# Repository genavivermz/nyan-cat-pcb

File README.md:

# nyancat PCB ₍^. .^₎⟆
made with KiCad; flat components for more lightweight use (as keychain or for general decoration!)

# design
- ordering with white solder mask + black silkscreen
- shiny tail design, made with decorative copper tracks + lines stacked on top
- colorful lights running a chasing pattern (powered by ATtiny10 microcontroller)

# preview

&nbsp

# schematics

# pcb editor

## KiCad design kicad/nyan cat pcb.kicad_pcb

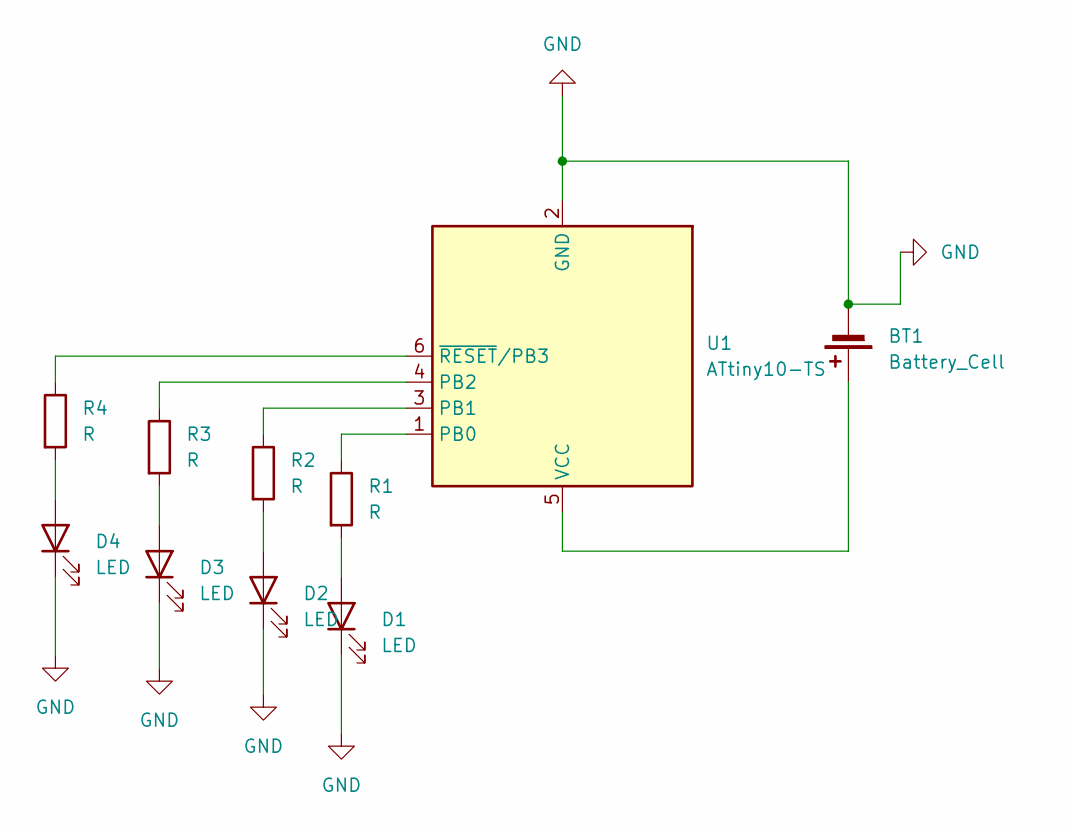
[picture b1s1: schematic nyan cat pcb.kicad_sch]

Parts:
BT1: Battery_Cell; BatteryHolder_LINX_BAT-HLD-012-SMT
D1, D2, D3, D4: LED; LED_0603_1608Metric
R1, R2, R3, R4: R; R_0603_1608Metric
U1: ATtiny10-TS; SOT-23-6

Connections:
GND: BT1.2 (-), D1.1 (K), D2.1 (K), D3.1 (K), D4.1 (K), U1.2 (GND)
unnamed: BT1.1 (+), U1.5 (VCC)
unnamed: D1.2 (A), R1.2
unnamed: D2.2 (A), R2.2
unnamed: D3.2 (A), R3.2
unnamed: D4.2 (A), R4.2
unnamed: R1.1, U1.1 (PB0)
unnamed: R2.1, U1.3 (PB1)
unnamed: R3.1, U1.4 (PB2)
unnamed: R4.1, U1.6 (~RESET/PB3)

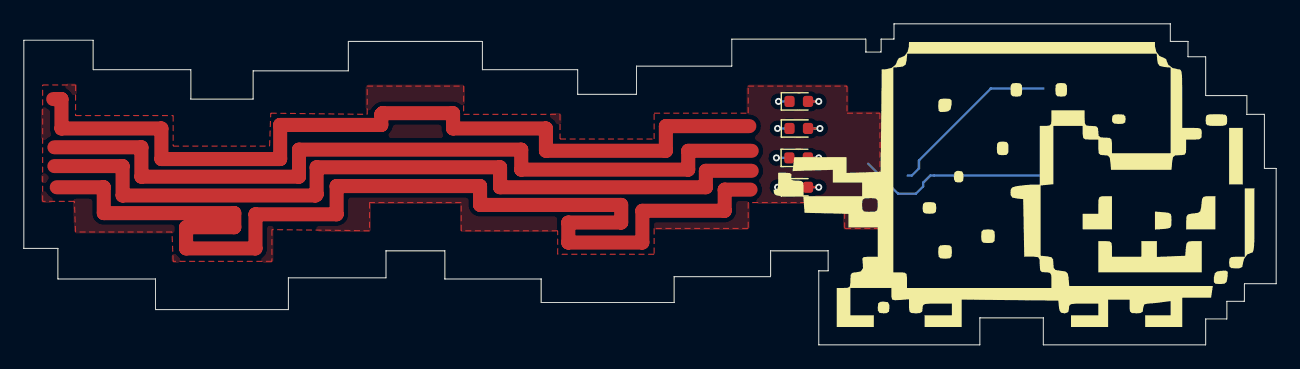
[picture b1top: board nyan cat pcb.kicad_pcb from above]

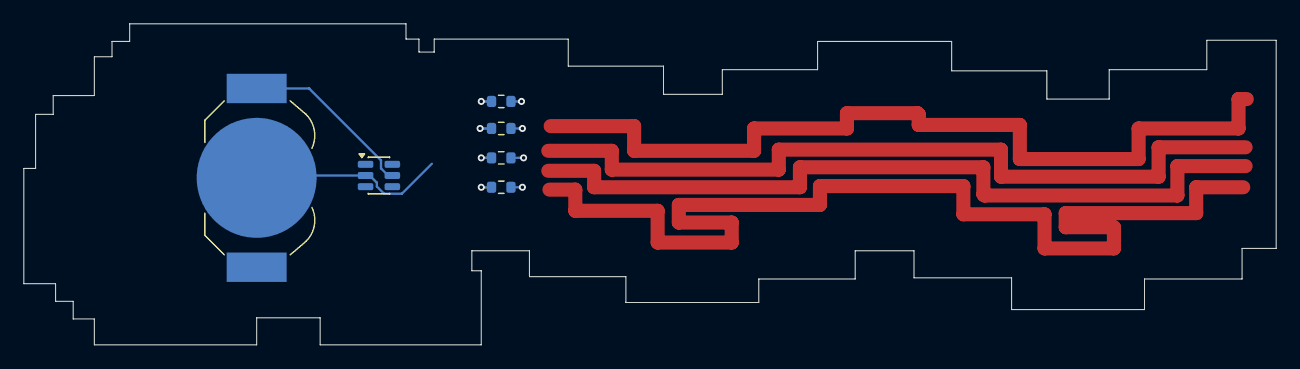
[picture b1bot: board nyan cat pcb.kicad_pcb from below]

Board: 2 copper layers, 106.5 x 27.3 mm, 10 parts (6 on the bottom side), 10 nets.

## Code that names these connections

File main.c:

#define F_CPU 1000000UL // default chip speed (1MHz)
#include <avr/io.h>
#include <util/delay.h>

int main(void) {
    // pins connected to the 4 leds
    DDRB |= (1 << PB0) | (1 << PB1) | (1 << PB2) | (1 << PB3);
    
    while(1) {
        // tail rainbow loop
        PORTB = (1 << PB0); // turn ON LED 1, others OFF
        _delay_ms(100);     // 100 millisecond pause
        
        PORTB = (1 << PB1); // turn ON LED 2, others OFF
        _delay_ms(100);
        
        PORTB = (1 << PB2); // turn ON LED 3, others OFF
        _delay_ms(100);
        
        PORTB = (1 << PB3); // turn ON LED 4, others OFF
        _delay_ms(100);
    }
}

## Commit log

2026-06-12 initial upload: hardware, images, code file
2026-06-12 preview pics + gif
2026-06-12 Rename 610B22C5-8725-4FF3-B76E-30D52C15D504.png to front_view.png
2026-06-12 Rename F6433F9A-60BC-49A7-90CE-E7421494E052.png to pcb_editor_view.png
2026-06-12 Rename F2F821BA-CD46-4D94-AD7A-9BC2E971F00C.png to back-view.png
2026-06-12 Rename pcb_editor_view.png to pcb-editor-view.png
2026-06-12 Rename front_view.png to front-view.png
2026-06-12 Rename B9803073-91F9-425B-B584-8F611CB63E0C.png to schematic-view.png
2026-06-12 Revise README for nyan cat PCB project
    Updated project description and added design, preview, schematics, and PCB editor sections with images.
2026-06-12 Update README.md
    Updated image source from PNG to GIF for better quality.
2026-06-12 Update README.md
    Reduced image width in README for better layout.
2026-06-12 Add LED cycling functionality in main.c
    Implement a simple LED cycling program for AVR.
2026-06-12 Update and rename main.c to main.cpp
    Updated main function to use 'true' in while loop and added return statement.
2026-06-12 organizing
2026-06-12 Update README.md
    Updated image path for back view in README.
